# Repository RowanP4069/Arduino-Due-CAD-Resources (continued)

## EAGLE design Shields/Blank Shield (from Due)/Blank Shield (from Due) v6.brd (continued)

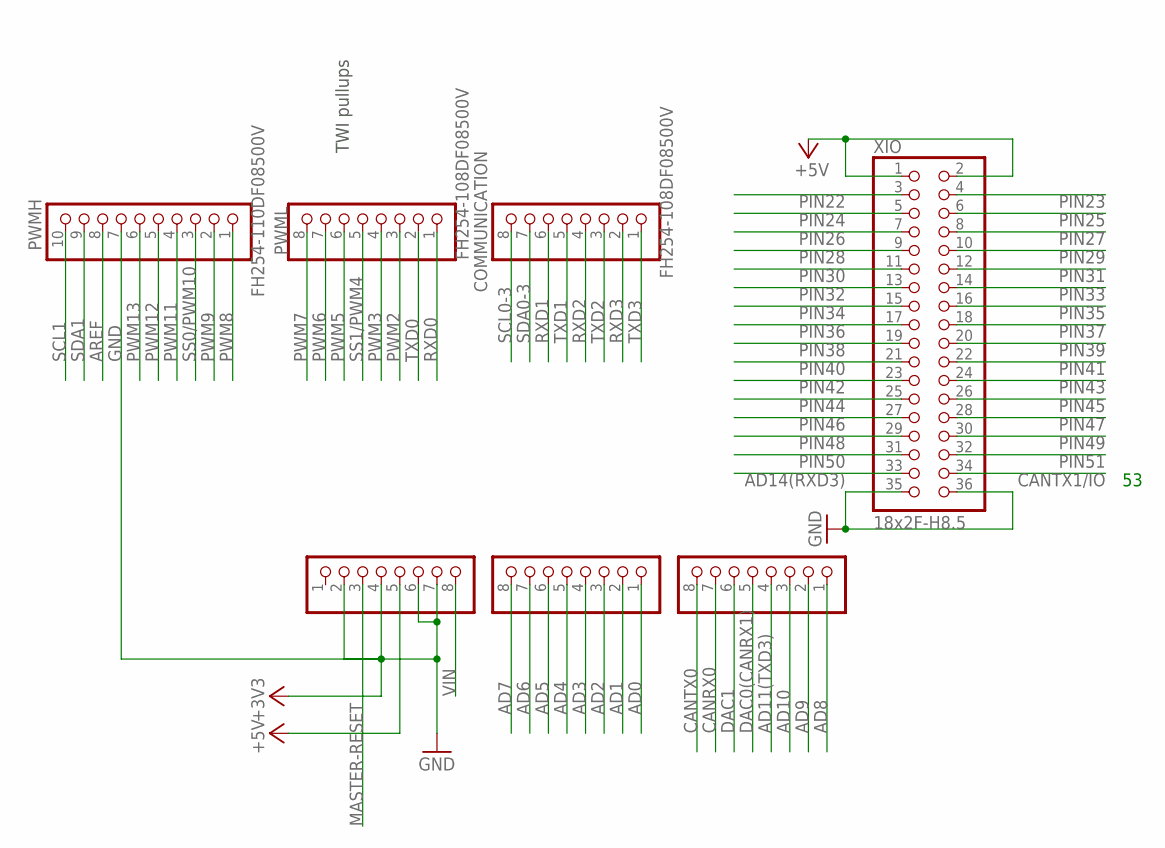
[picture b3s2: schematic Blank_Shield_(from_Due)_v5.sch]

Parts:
ADCH: FH254-108DF08500V; 1X08
ADCL: FH254-108DF08500V; 1X08
COMMUNICATION: FH254-108DF08500V; 1X08
POWER: FH254-108DF08500V; 1X08
PWMH: FH254-110DF08500V; 1X10
PWML: FH254-108DF08500V; 1X08
XIO: 18x2F-H8.5; 2X18

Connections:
+3V3: POWER.2, POWER.4
+5V: POWER.5, XIO.1, XIO.2
AD0: ADCL.1
AD1: ADCL.2
AD2: ADCL.3
AD3: ADCL.4
AD4: ADCL.5
AD5: ADCL.6
AD6: ADCL.7
AD7: ADCL.8
AD8: ADCH.1
AD9: ADCH.2
AD10: ADCH.3
AD11(TXD3): ADCH.4
AD14(RXD3): XIO.33
AREF: PWMH.8
CANRX0: ADCH.7
CANTX0: ADCH.8
CANTX1/IO: XIO.34
DAC0(CANRX1): ADCH.5
DAC1: ADCH.6
GND: POWER.6, POWER.7, PWMH.7, XIO.35, XIO.36
PIN22: XIO.3
PIN23: XIO.4
PIN24: XIO.5
PIN25: XIO.6
PIN26: XIO.7
PIN27: XIO.8
PIN28: XIO.9
PIN29: XIO.10
PIN30: XIO.11
PIN31: XIO.12
PIN32: XIO.13
PIN33: XIO.14
PIN34: XIO.15
PIN35: XIO.16
PIN36: XIO.17
PIN37: XIO.18
PIN38: XIO.19
PIN39: XIO.20
PIN40: XIO.21
PIN41: XIO.22
PIN42: XIO.23
PIN43: XIO.24
PIN44: XIO.25
PIN45: XIO.26
PIN46: XIO.27
PIN47: XIO.28
PIN48: XIO.29
PIN49: XIO.30
PIN50: XIO.31
PIN51: XIO.32
PWM2: PWML.3
PWM3: PWML.4
PWM5: PWML.6
PWM6: PWML.7
PWM7: PWML.8
PWM8: PWMH.1
PWM9: PWMH.2
PWM11: PWMH.4
PWM12: PWMH.5
PWM13: PWMH.6
RXD0: PWML.1
RXD1: COMMUNICATION.6
RXD2: COMMUNICATION.4
RXD3: COMMUNICATION.2
SCL0-3: COMMUNICATION.8
SCL1: PWMH.10
SDA0-3: COMMUNICATION.7
SDA1: PWMH.9
SS0/PWM10: PWMH.3
SS1/PWM4: PWML.5
TXD0: PWML.2
TXD1: COMMUNICATION.5
TXD2: COMMUNICATION.3
TXD3: COMMUNICATION.1
VIN: POWER.8

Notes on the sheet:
TWI pullups

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
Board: 2 copper layers, 7 parts (0 on the bottom side), 3 nets, no tracks yet.
